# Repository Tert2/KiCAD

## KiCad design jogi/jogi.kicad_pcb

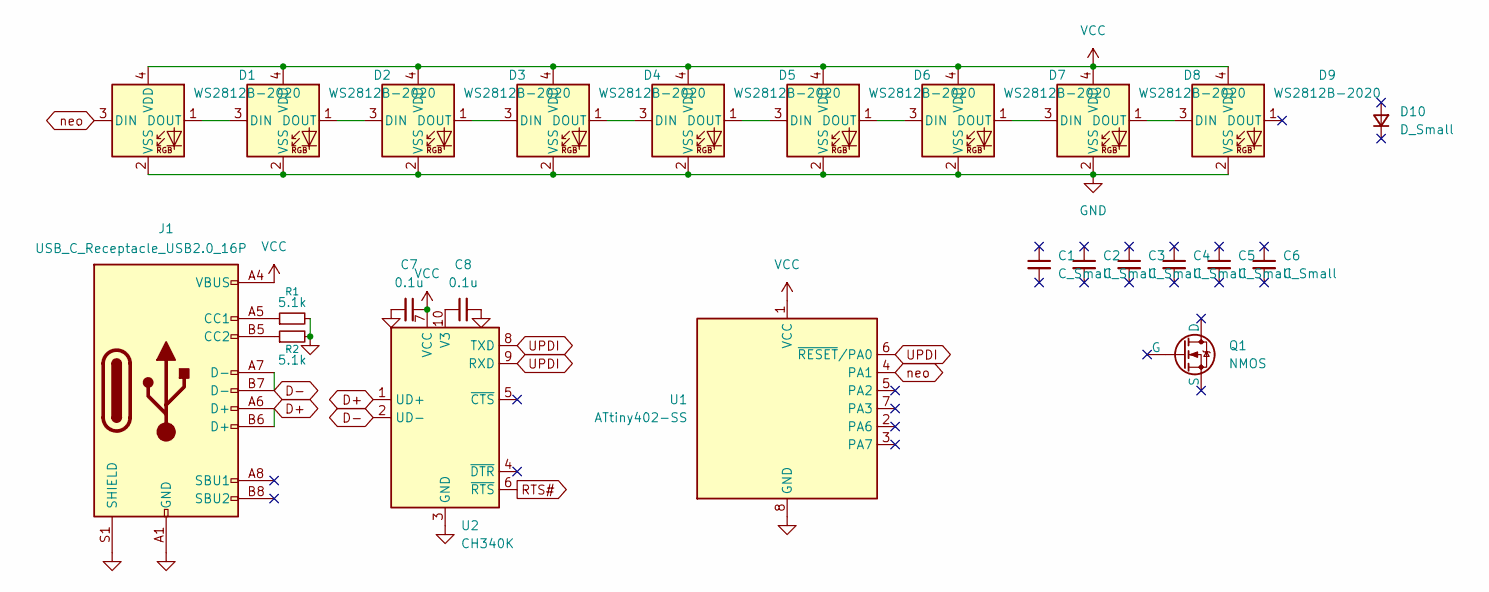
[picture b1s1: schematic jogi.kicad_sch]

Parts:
C1: C_Small; C_1210_3225Metric
C2: C_Small; C_1206_3216Metric
C3: C_Small; C_0805_2012Metric
C4: C_Small; C_0603_1608Metric
C5: C_Small; C_0402_1005Metric
C6: C_Small; C_01005_0402Metric
C7, C8: 0.1u; C_0603_1608Metric_Pad1.08x0.95mm_HandSolder
D1, D2, D3, D4, D5, D6, D7, D8, D9: WS2812B-2020; LED_WS2812B-2020_PLCC4_2.0x2.0mm
D10: D_Small; Nexperia_CFP3_SOD-123W
J1: USB_C_Receptacle_USB2.0_16P; USB_C_Receptacle_GCT_USB4105-xx-A_16P_TopMnt_Horizontal
Q1: NMOS; TSOT-23
R1, R2: 5.1k; R_0603_1608Metric_Pad0.98x0.95mm_HandSolder
U1: ATtiny402-SS; SOIC-8_3.9x4.9mm_P1.27mm
U2: CH340K; SSOP-10-1EP_3.9x4.9mm_P1mm_EP2.1x3.3mm

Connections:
D+: J1.A6 (D+), J1.B6 (D+), U2.1 (UD+)
D-: J1.A7 (D-), J1.B7 (D-), U2.2 (UD-)
GND: C7.2, C8.2, D1.2 (VSS), D2.2 (VSS), D3.2 (VSS), D4.2 (VSS), D5.2 (VSS), D6.2 (VSS), D7.2 (VSS), D8.2 (VSS), D9.2 (VSS), J1.A1 (GND), J1.A12 (GND), J1.B1 (GND), J1.B12 (GND), J1.S1 (SHIELD), R1.2, R2.2, U1.8 (GND), U2.3 (GND), U2.11 (GND)
unnamed: D1.1 (DOUT), D2.3 (DIN)
unnamed: D2.1 (DOUT), D3.3 (DIN)
unnamed: D3.1 (DOUT), D4.3 (DIN)
unnamed: D4.1 (DOUT), D5.3 (DIN)
unnamed: D5.1 (DOUT), D6.3 (DIN)
unnamed: D6.1 (DOUT), D7.3 (DIN)
unnamed: D7.1 (DOUT), D8.3 (DIN)
unnamed: D8.1 (DOUT), D9.3 (DIN)
unnamed: J1.A5 (CC1), R1.1
unnamed: J1.B5 (CC2), R2.1
unnamed: C8.1, U2.10 (V3)
RTS#: U2.6 (~RTS)
UPDI: U1.6 (~RESET/PA0), U2.8 (TXD), U2.9 (RXD)
VCC: C7.1, D1.4 (VDD), D2.4 (VDD), D3.4 (VDD), D4.4 (VDD), D5.4 (VDD), D6.4 (VDD), D7.4 (VDD), D8.4 (VDD), D9.4 (VDD), J1.A4 (VBUS), J1.A9 (VBUS), J1.B4 (VBUS), J1.B9 (VBUS), U1.1 (VCC), U2.7 (VCC)
neo: D1.3 (DIN), U1.4 (PA1)

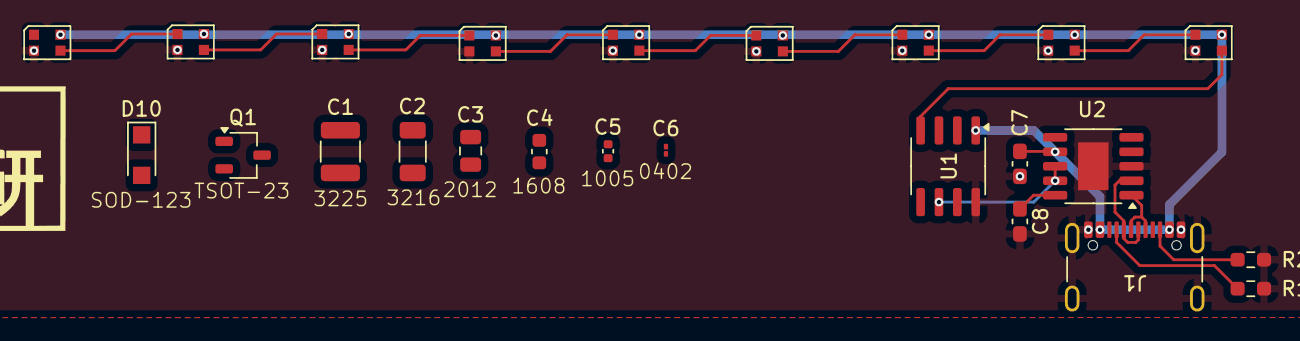
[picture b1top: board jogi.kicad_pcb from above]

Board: 2 copper layers, 24 parts (0 on the bottom side), 17 nets.

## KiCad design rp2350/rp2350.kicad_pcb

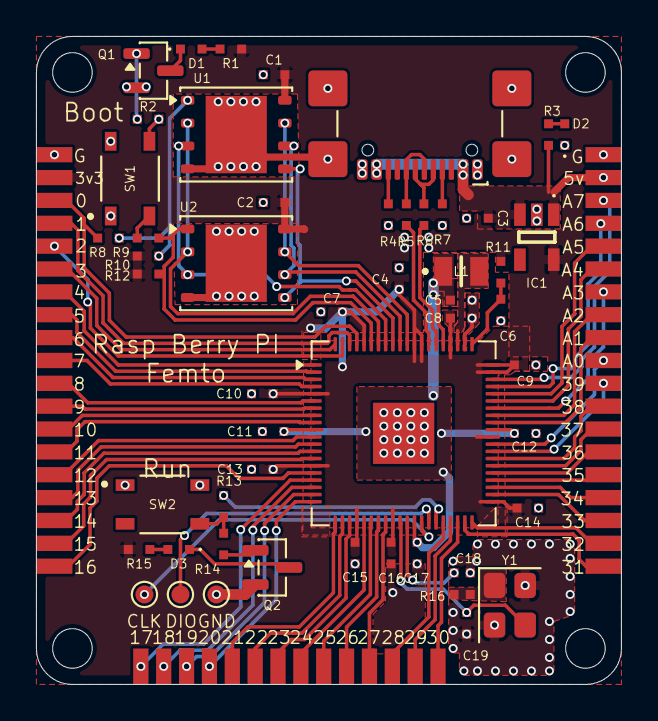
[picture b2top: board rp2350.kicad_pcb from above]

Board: 2 copper layers, 32.5 x 36.0 mm, 59 parts (0 on the bottom side), 83 nets.

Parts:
C1, C2, C4, C7, C10, C11, C12, C13, C14, C15, C16, C17: 0.1u; 1005
C3, C9: 1u; 1005
C5, C6, C8: 4.7u; 1005
C18, C19: 15p; 1005
D1, D2, D3: LED_Small; D1005
IC1: RT9080N-08GJ5; SOT94P280X100-5N
J1: USB_C_Receptacle_USB2.0_16P; USB_C_Receptacle_GCT_USB4110
J2, J3: Conn_01x19_Pin; 01x19
J4, J5, J6: Conn_01x01_Pin; TestPoint_Pad_D1.0mm
J7: Conn_01x14_Pin; 01x14
L1: AOTA-B201610S3R3-101-T; AOTAB201610S3R3101T
Q1, Q2: BSS138; SOT-23
R1, R3, R9, R13, R15, R16: 1k; R1005
R2, R14: 100k; R1005
R4, R7: 4.7k; R1005
R5, R6: 27; R1005
R8, R10, R12: 10k; R1005
R11: 33; R1005
REF1, REF2, REF3, REF4: MountingHole_2.2mm_M2
SW1, SW2: SKRPABE010; SW_SKRPABE010
U1, U2: W25Q128JVP; WSON-8-1EP_6x5mm_P1.27mm_EP3.4x4.3mm
U3: RP2350B; QFN-80-1EP_10x10mm_P0.4mm_EP3.4x3.4mm
Y1: 12M; Crystal_SMD_3225-4Pin_3.2x2.5mm

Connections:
+1V1: C5.1, C11.2, C12.2, C17.2, L1.1, U3.10 (DVDD), U3.32 (DVDD), U3.51 (DVDD), U3.65 (VREG_FB)
+3V3: C1.1, C2.1, C4.2, C7.2, C8.1, C9.2, C10.2, C13.2, C14.2, C15.2, C16.2, IC1.5 (VOUT), J2.18, R1.2, R10.2, R11.2, R12.2, R15.2, U1.8 (VCC), U2.8 (VCC), U3.5 (IOVDD), U3.15 (IOVDD), U3.24 (IOVDD), U3.29 (IOVDD), U3.41 (IOVDD), U3.50 (IOVDD), U3.59 (ADC_AVDD), U3.60 (IOVDD), U3.64 (VREG_VIN), U3.68 (USB_OTP_VDD), U3.69 (QSPI_IOVDD), U3.76 (IOVDD)
/ADC0: J3.10, U3.49 (GPIO40/ADC0)
/ADC1: J3.9, U3.52 (GPIO41/ADC1)
/ADC2: J3.8, U3.53 (GPIO42/ADC2)
/ADC3: J3.7, U3.54 (GPIO43/ADC3)
/ADC4: J3.6, U3.55 (GPIO44/ADC4)
/ADC5: J3.5, U3.56 (GPIO45/ADC5)
/ADC6: J3.4, U3.57 (GPIO46/ADC6)
/ADC7: J3.3, U3.58 (GPIO47/ADC7)
/FLASH2_SS: R8.2, R10.1, U1.1 (~CS)
/FLASH_SS: R9.2, R12.1, U2.1 (~CS), U3.75 (~QSPI_SS)
/IO0: J2.17, R8.1, U3.77 (GPIO0)
/IO1: J2.16, U3.78 (GPIO1)
/IO2: J2.15, U3.79 (GPIO2)
/IO3: J2.14, U3.80 (GPIO3)
/IO4: J2.13, U3.1 (GPIO4)
/IO5: J2.12, U3.2 (GPIO5)
/IO6: J2.11, U3.3 (GPIO6)
/IO7: J2.10, U3.4 (GPIO7)
/IO8: J2.9, U3.6 (GPIO8)
/IO9: J2.8, U3.7 (GPIO9)
/IO10: J2.7, U3.8 (GPIO10)
/IO11: J2.6, U3.9 (GPIO11)
/IO12: J2.5, U3.11 (GPIO12)
/IO13: J2.4, U3.12 (GPIO13)
/IO14: J2.3, U3.13 (GPIO14)
/IO15: J2.2, U3.14 (GPIO15)
/IO16: J2.1, U3.16 (GPIO16)
/IO17: J7.14, U3.17 (GPIO17)
/IO18: J7.13, U3.18 (GPIO18)
/IO19: J7.12, U3.19 (GPIO19)
/IO20: J7.11, U3.20 (GPIO20)
/IO21: J7.10, U3.21 (GPIO21)
/IO22: J7.9, U3.22 (GPIO22)
/IO23: J7.8, U3.23 (GPIO23)
/IO24: J7.7, U3.25 (GPIO24)
/IO25: J7.6, U3.26 (GPIO25)
/IO26: J7.5, U3.27 (GPIO26)
/IO27: J7.4, U3.28 (GPIO27)
/IO28: J7.3, U3.36 (GPIO28)
/IO29: J7.2, U3.37 (GPIO29)
/IO30: J7.1, U3.38 (GPIO30)
/IO31: J3.19, U3.39 (GPIO31)
/IO32: J3.18, U3.40 (GPIO32)
/IO33: J3.17, U3.42 (GPIO33)
/IO34: J3.16, U3.43 (GPIO34)
/IO35: J3.15, U3.44 (GPIO35)
/IO36: J3.14, U3.45 (GPIO36)
/IO37: J3.13, U3.46 (GPIO37)
/IO38: J3.12, U3.47 (GPIO38)
/IO39: J3.11, U3.48 (GPIO39)
/QSPI_SCLK: U1.6 (CLK), U2.6 (CLK), U3.71 (QSPI_SCLK)
/QSPI_SD0: U1.5 (DI/IO_{0}), U2.5 (DI/IO_{0}), U3.72 (QSPI_SD0)
/QSPI_SD1: U1.2 (DO/IO_{1}), U2.2 (DO/IO_{1}), U3.74 (QSPI_SD1)
/QSPI_SD2: U1.3 (~WP/IO_{2}), U2.3 (~WP/IO_{2}), U3.73 (QSPI_SD2)
/QSPI_SD3: U1.7 (~HOLD/~RESET/IO_{3}), U2.7 (~HOLD/~RESET/IO_{3}), U3.70 (QSPI_SD3)
/RUN: R13.2, U3.35 (RUN)
/SWCLK: J4.1, U3.33 (SWCLK)
/SWDIO: J5.1, U3.34 (SWDIO)
/XIN: C19.2, U3.30 (XIN), Y1.3
/XOUT: R16.2, U3.31 (XOUT)
/xout: C18.2, R16.1, Y1.1
D+: R5.2, U3.67 (USB_DP)
D-: R6.2, U3.66 (USB_DM)
GND: C1.2, C2.2, C3.1, C4.1, C5.2, C6.2, C7.1, C8.2, C9.1, C10.1, C11.1, C12.1, C13.1, C14.1, C15.1, C16.1, C17.1, C18.1, C19.1, D2.1 (K), IC1.2 (GND), J1.A1 (GND), J1.A12 (GND), J1.B1 (GND), J1.B12 (GND), J1.S1 (SHIELD), J2.19, J3.1, J6.1, Q1.2 (S), Q2.2 (S), R4.2, R7.2, SW1.1, SW1.2, SW2.1, SW2.2, U1.4 (GND), U1.9 (EP), U2.4 (GND), U2.9 (EP), U3.62 (VREG_PGND), U3.81 (GND), Y1.2 (G), Y1.4 (G)
unnamed: D3.2 (A), R15.1
unnamed: D3.1 (K), Q2.3 (D)
unnamed: D1.2 (A), R1.1
unnamed: D1.1 (K), Q1.3 (D)
unnamed: D2.2 (A), R3.1
unnamed: J1.A5 (CC1), R7.1
unnamed: J1.B5 (CC2), R4.1
unnamed: J1.A6 (D+), J1.B6 (D+), R5.1
unnamed: J1.A7 (D-), J1.B7 (D-), R6.1
unnamed: Q2.1 (G), R14.1
unnamed: Q1.1 (G), R2.2
unnamed: R13.1, R14.2, SW2.4 (A)
unnamed: R2.1, SW1.4 (A)
unnamed: R9.1, SW1.3 (K)
unnamed: C6.1, R11.1, U3.61 (VREG_AVDD)
unnamed: L1.2, U3.63 (VREG_LX)
VBUS: C3.2, IC1.1 (VIN), IC1.3 (EN), J1.A4 (VBUS), J1.A9 (VBUS), J1.B4 (VBUS), J1.B9 (VBUS), J3.2, R3.2

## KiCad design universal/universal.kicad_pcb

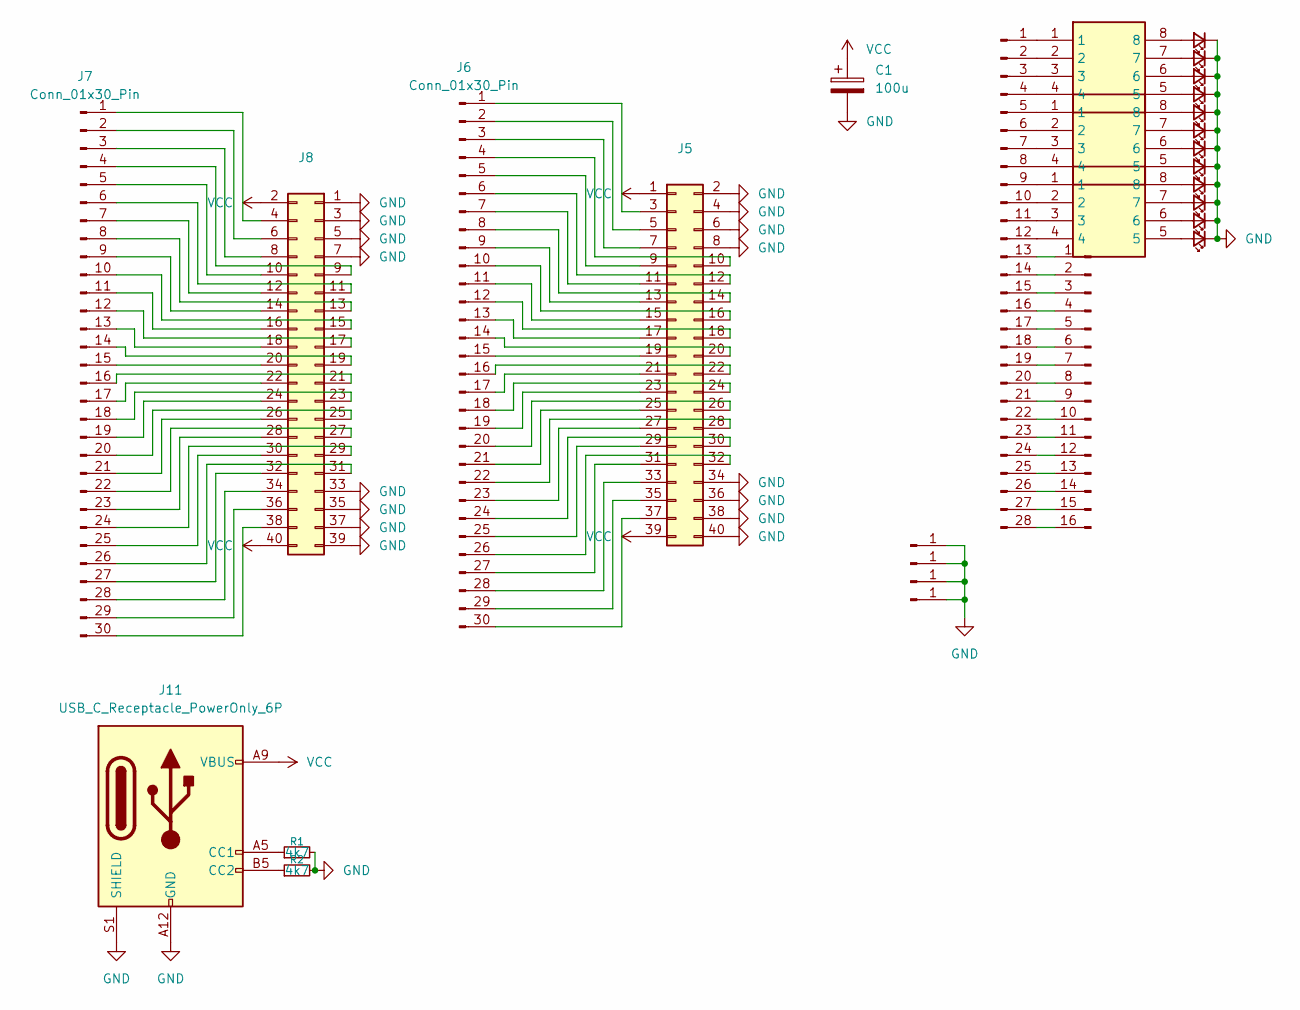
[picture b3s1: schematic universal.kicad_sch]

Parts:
C1: 100u; CP_Radial_D6.3mm_P2.50mm
D1, D2, D3, D4, D5, D6, D7, D8, D9, D10, D11, D12: LED_Small; LED_0603_1608Metric
J1, J2, J3, J4: Conn_01x01_Pin; MountingHole_3.2mm_M3_DIN965_Pad_TopBottom
J5, J8: Conn_02x20_Odd_Even; PinHeader_2x20_P2.54mm_Vertical
J6, J7: Conn_01x30_Pin; SMD_uni
J9: Conn_01x28_Pin; SMD_28_uni
J10: Conn_01x16_Pin; PinHeader_1x16_P2.54mm_Vertical
J11: USB_C_Receptacle_PowerOnly_6P; USB_C_Receptacle_GCT_USB4125-xx-x-0190_6P_TopMnt_Horizontal
R1, R2: 4k7; R_0603_1608Metric
RN1, RN2, RN3: BCN164AB220J7; Manufacturer_Part_Number BCN164AB220J7; Mouser Part Number 858-BCN164AB220J7

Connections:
GND: C1.2, D1.1 (K), D2.1 (K), D3.1 (K), D4.1 (K), D5.1 (K), D6.1 (K), D7.1 (K), D8.1 (K), D9.1 (K), D10.1 (K), D11.1 (K), D12.1 (K), J1.1, J2.1, J3.1, J4.1, J5.2, J5.4, J5.6, J5.8, J5.34, J5.36, J5.38, J5.40, J8.1, J8.3, J8.5, J8.7, J8.33, J8.35, J8.37, J8.39, J11.A12 (GND), J11.B12 (GND), J11.S1 (SHIELD), R1.2, R2.2
unnamed: D1.2 (A), RN1.8
unnamed: D2.2 (A), RN1.7
unnamed: D3.2 (A), RN1.6
unnamed: D4.2 (A), RN1.5
unnamed: D5.2 (A), RN2.8
unnamed: D6.2 (A), RN2.7
unnamed: D7.2 (A), RN2.6
unnamed: D8.2 (A), RN2.5
unnamed: D9.2 (A), RN3.8
unnamed: D10.2 (A), RN3.7
unnamed: D11.2 (A), RN3.6
unnamed: D12.2 (A), RN3.5
unnamed: J5.3, J6.1
unnamed: J5.5, J6.2
unnamed: J5.7, J6.3
unnamed: J5.9, J6.5
unnamed: J5.10, J6.4
unnamed: J5.11, J6.7
unnamed: J5.12, J6.6
unnamed: J5.13, J6.9
unnamed: J5.14, J6.8
unnamed: J5.15, J6.11
unnamed: J5.16, J6.10
unnamed: J5.17, J6.13
unnamed: J5.18, J6.12
unnamed: J5.19, J6.15
unnamed: J5.20, J6.14
unnamed: J5.21, J6.17
unnamed: J5.22, J6.16
unnamed: J5.23, J6.19
unnamed: J5.24, J6.18
unnamed: J5.25, J6.21
unnamed: J5.26, J6.20
unnamed: J5.27, J6.23
unnamed: J5.28, J6.22
unnamed: J5.29, J6.25
unnamed: J5.30, J6.24
unnamed: J5.31, J6.27
unnamed: J5.32, J6.26
unnamed: J5.33, J6.28
unnamed: J5.35, J6.29
unnamed: J5.37, J6.30
unnamed: J7.1, J8.4
unnamed: J7.2, J8.6
unnamed: J7.3, J8.8
unnamed: J7.4, J8.9
unnamed: J7.5, J8.10
unnamed: J7.6, J8.11
unnamed: J7.7, J8.12
unnamed: J7.8, J8.13
unnamed: J7.9, J8.14
unnamed: J7.10, J8.15
unnamed: J7.11, J8.16
unnamed: J7.12, J8.17
unnamed: J7.13, J8.18
unnamed: J7.14, J8.19
unnamed: J7.15, J8.20
unnamed: J7.16, J8.21
unnamed: J7.17, J8.22
unnamed: J7.18, J8.23
unnamed: J7.19, J8.24
unnamed: J7.20, J8.25
unnamed: J7.21, J8.26
unnamed: J7.22, J8.27
unnamed: J7.23, J8.28
unnamed: J7.24, J8.29
unnamed: J7.25, J8.30
unnamed: J7.26, J8.31
unnamed: J7.27, J8.32
unnamed: J7.28, J8.34
unnamed: J7.29, J8.36
unnamed: J7.30, J8.38
unnamed: J9.1, RN1.1
unnamed: J9.2, RN1.2
unnamed: J9.3, RN1.3
unnamed: J9.4, RN1.4
unnamed: J9.5, RN2.1
unnamed: J9.6, RN2.2
unnamed: J9.7, RN2.3
unnamed: J9.8, RN2.4
unnamed: J9.9, RN3.1
unnamed: J9.10, RN3.2
unnamed: J9.11, RN3.3
unnamed: J9.12, RN3.4
unnamed: J9.13, J10.1
unnamed: J9.14, J10.2
unnamed: J9.15, J10.3
unnamed: J9.16, J10.4
unnamed: J9.17, J10.5
unnamed: J9.18, J10.6
unnamed: J9.19, J10.7
unnamed: J9.20, J10.8
unnamed: J9.21, J10.9
unnamed: J9.22, J10.10
unnamed: J9.23, J10.11
unnamed: J9.24, J10.12
unnamed: J9.25, J10.13
unnamed: J9.26, J10.14
unnamed: J9.27, J10.15
unnamed: J9.28, J10.16
unnamed: J11.A5 (CC1), R1.1
unnamed: J11.B5 (CC2), R2.1
VCC: C1.1, J5.1, J5.39, J8.2, J8.40, J11.A9 (VBUS), J11.B9 (VBUS)

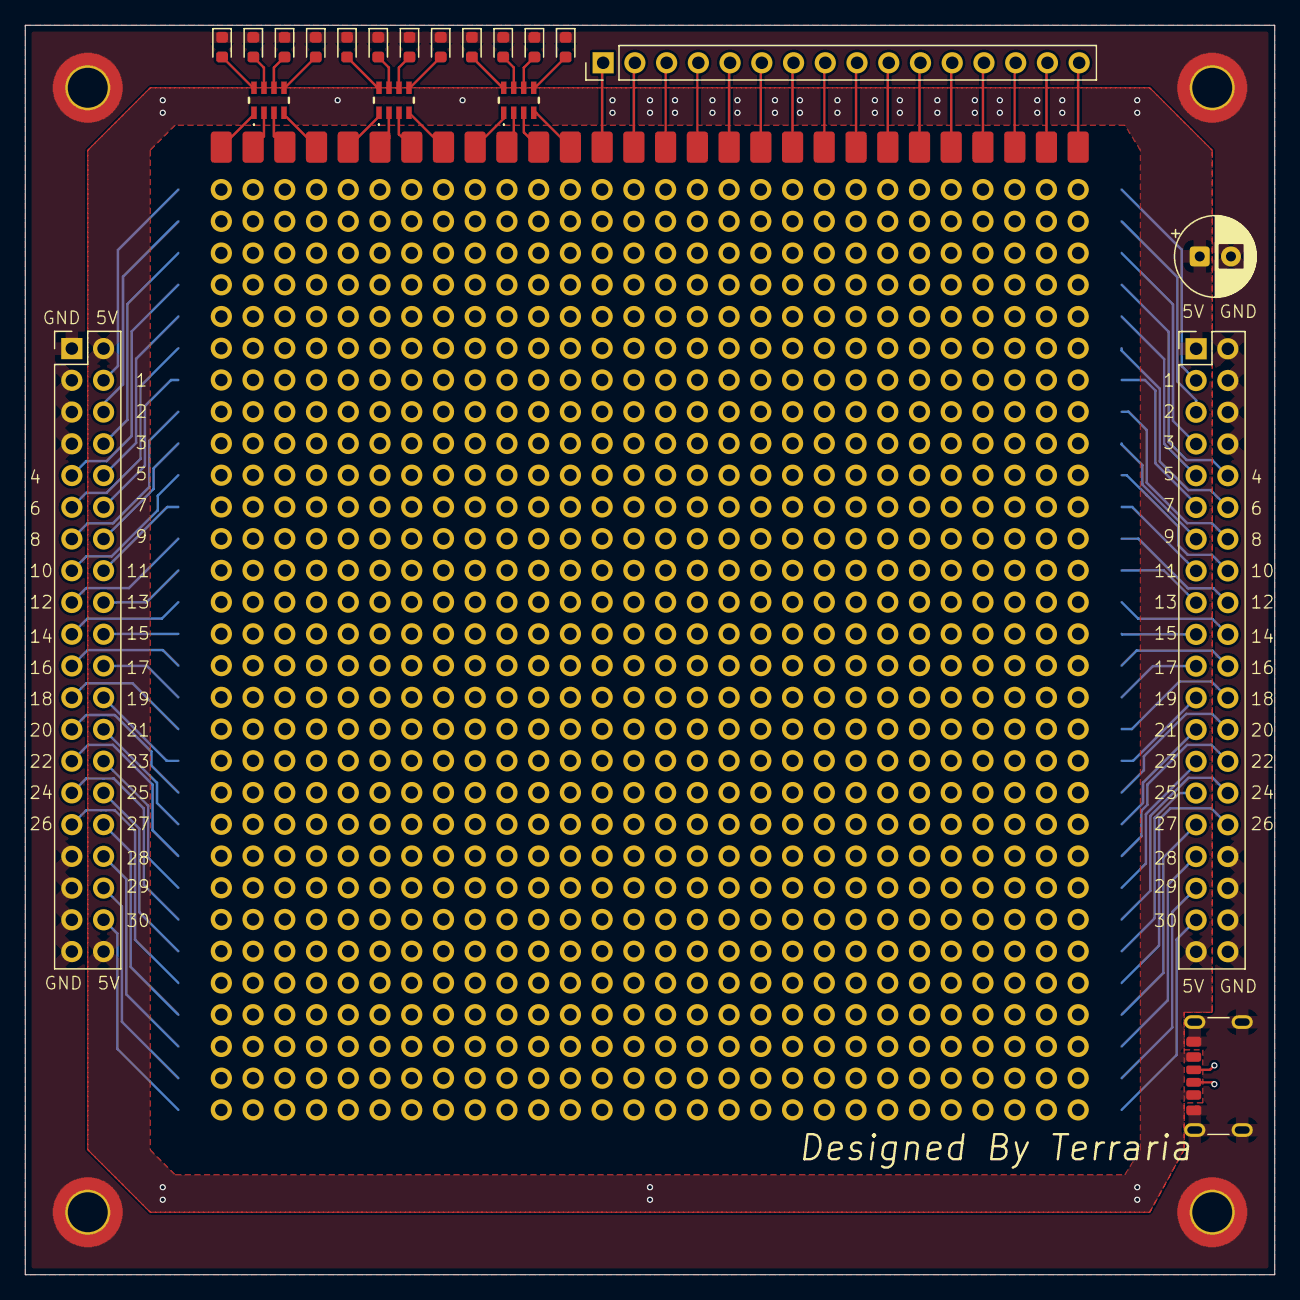
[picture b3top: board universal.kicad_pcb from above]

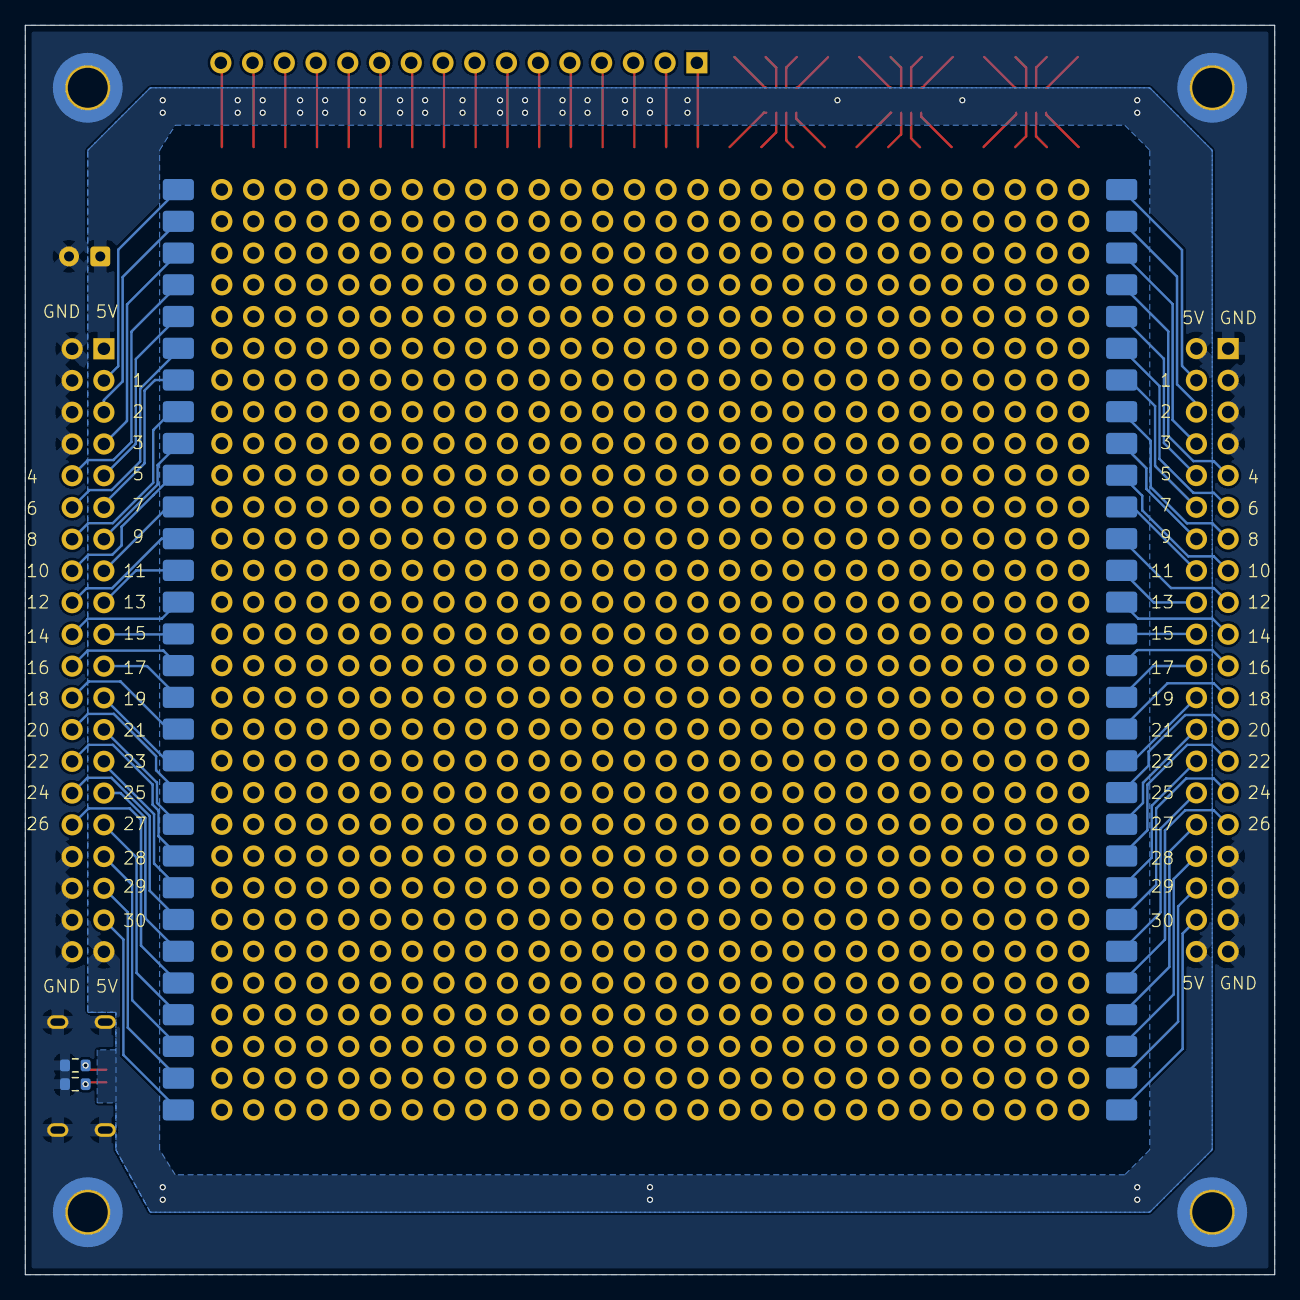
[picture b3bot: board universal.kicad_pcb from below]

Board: 2 copper layers, 100.0 x 100.0 mm, 29 parts (4 on the bottom side), 104 nets.

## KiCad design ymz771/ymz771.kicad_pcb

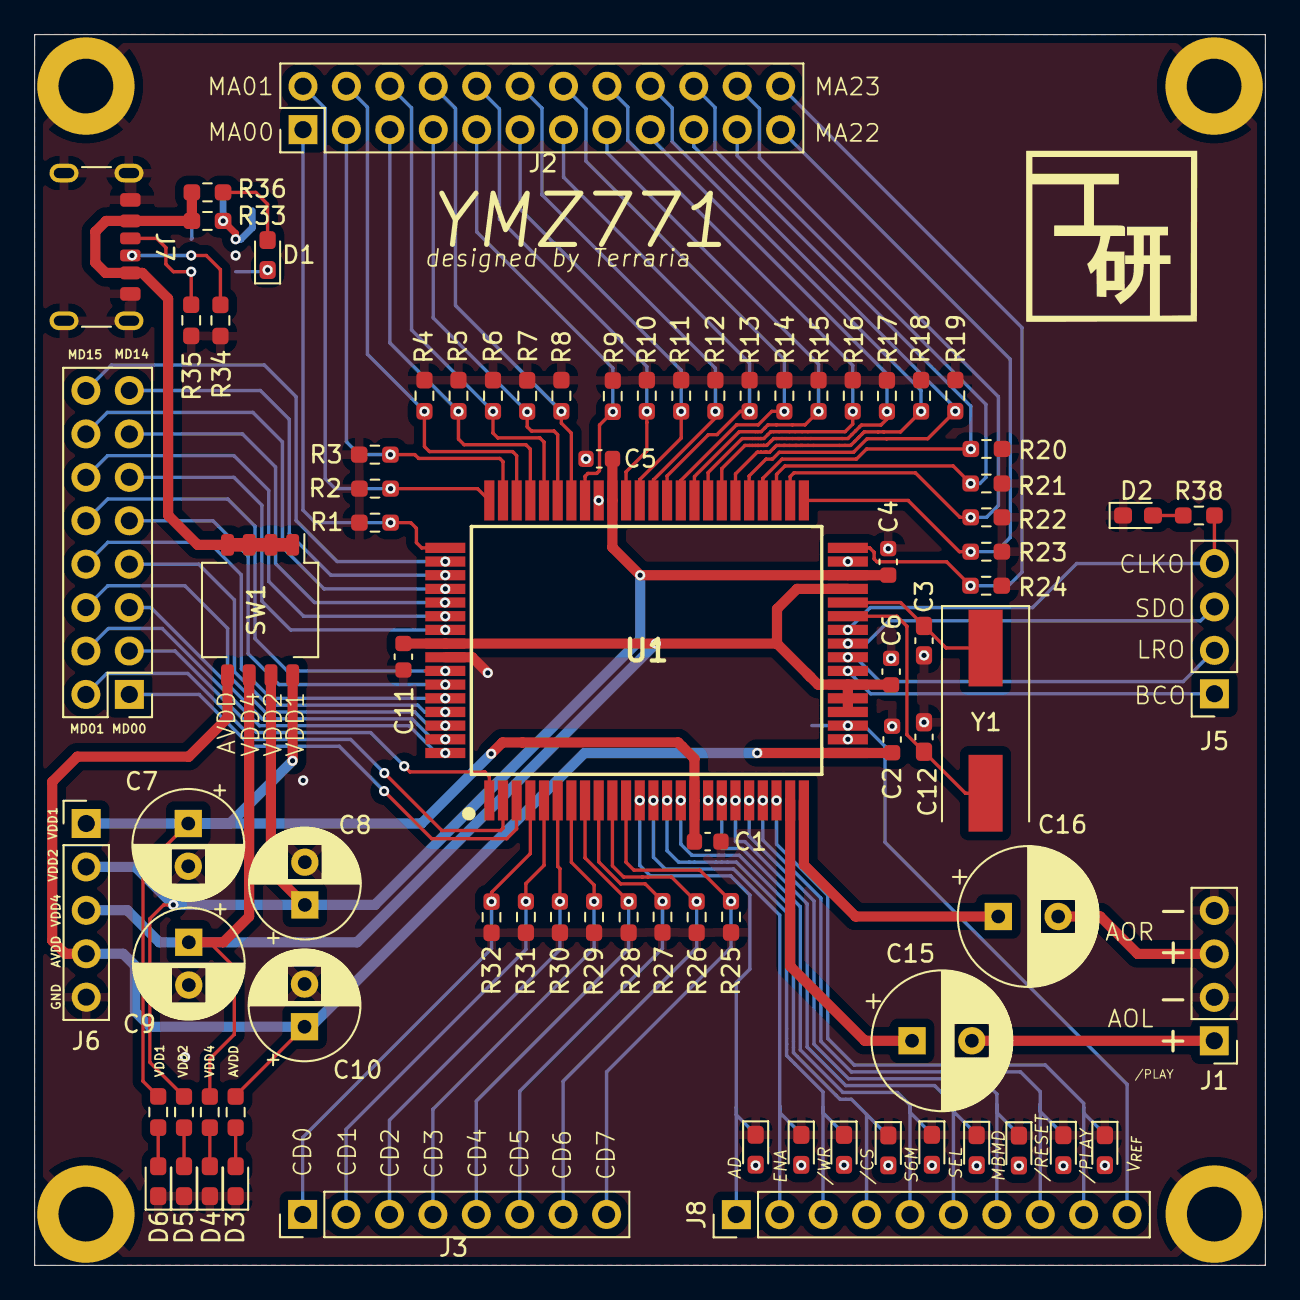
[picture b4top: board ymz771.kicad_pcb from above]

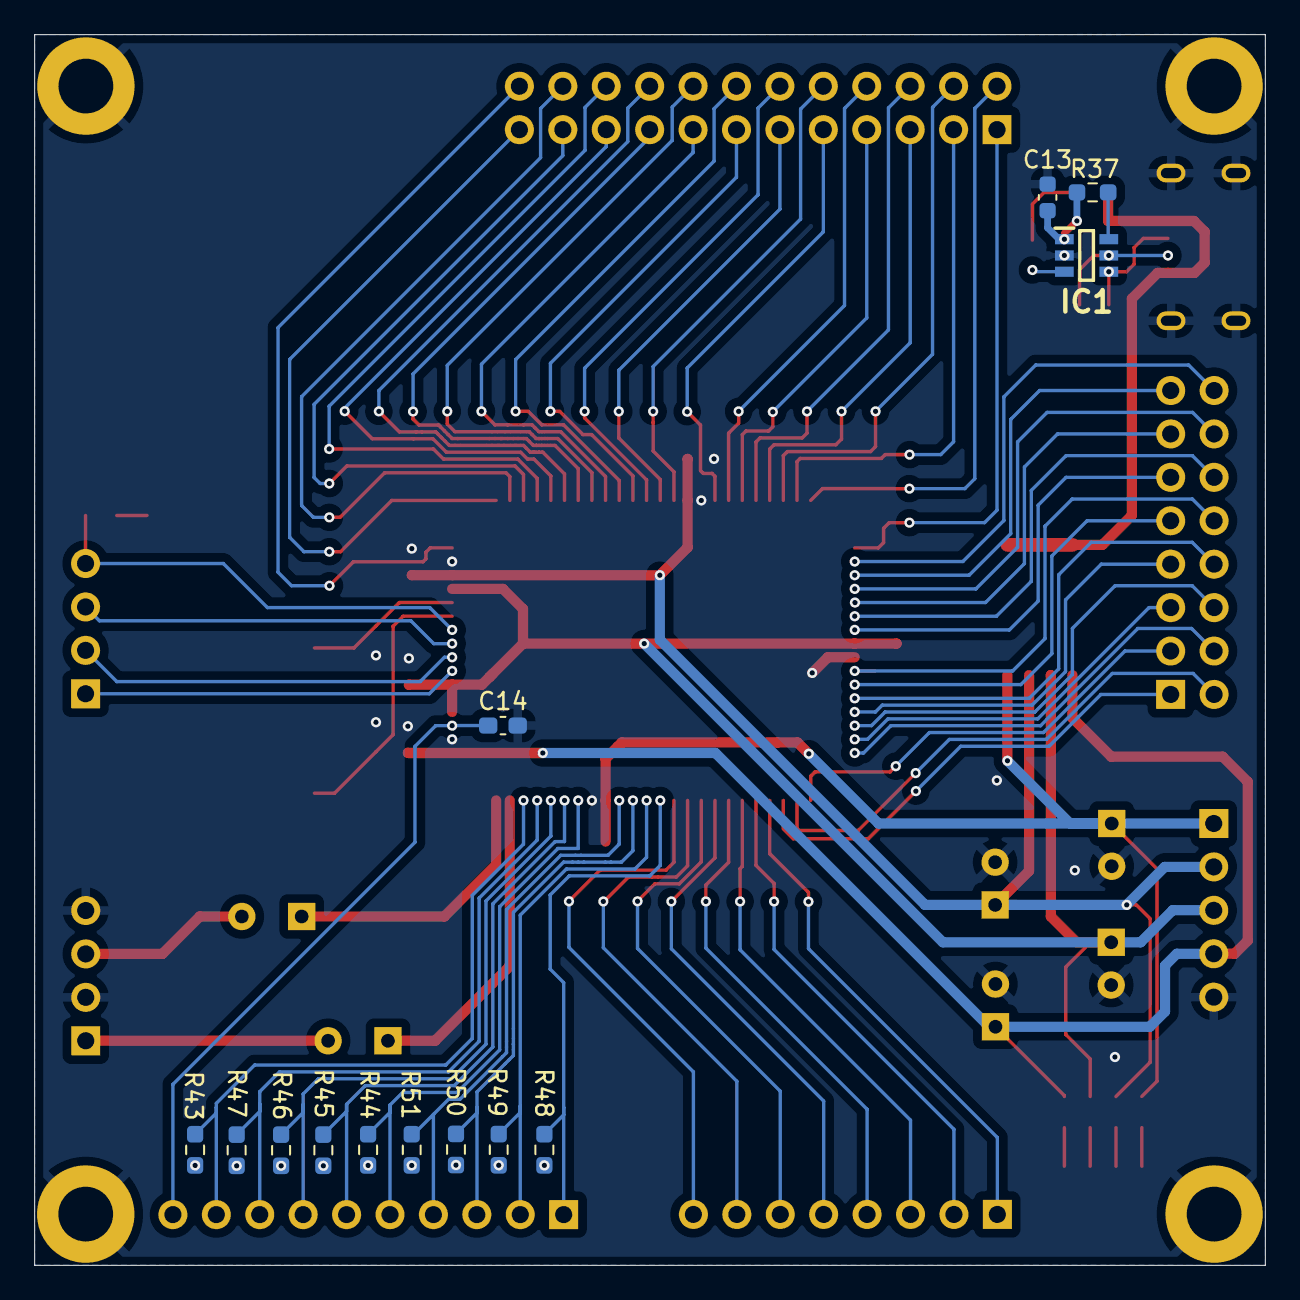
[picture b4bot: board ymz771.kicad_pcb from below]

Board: 2 copper layers, 72.0 x 72.0 mm, 94 parts (13 on the bottom side), 94 nets.

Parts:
C1, C2, C4, C5, C6, C11, C13: C_Small; C_0603_1608Metric
C3, C12, C14: 20n; C_0603_1608Metric_Pad1.08x0.95mm_HandSolder
C7, C8, C9, C10: C_Polarized_Small; CP_Radial_D6.3mm_P2.50mm
C15, C16: C_Polarized_Small; CP_Radial_D8.0mm_P3.50mm
D1, D2, D3, D4, D5, D6, D7, D8, D9, D10, D11, D12, D13, D14, D15: LED_Small; LED_0603_1608Metric_Pad1.05x0.95mm_HandSolder
IC1: CH221K; SOT95P280X120-6N
J1: Conn_01x04_Pin; PinHeader_1x04_P2.54mm_Vertical
J2: Conn_02x12_Counter_Clockwise; PinHeader_2x12_P2.54mm_Vertical
J3: Conn_01x08_Pin; PinHeader_1x08_P2.54mm_Vertical
J4: Conn_02x08_Counter_Clockwise; PinHeader_2x08_P2.54mm_Vertical
J5: Conn_01x04_Pin; PinSocket_1x04_P2.54mm_Vertical
J6: Conn_01x05_Pin; PinHeader_1x05_P2.54mm_Vertical
J7: USB_C_Receptacle_PowerOnly_6P; USB_C_Receptacle_GCT_USB4125-xx-x_6P_TopMnt_Horizontal
J8: Conn_01x10_Pin; PinHeader_1x10_P2.54mm_Vertical
R1, R2, R3, R4, R5, R6, R7, R8, R9, R10, R11, R12, R13, R14, R15, R16, R17, R18, R19, R20, R21, R22, R23, R24, R25, R26, R27, R28, R29, R30, R31, R32, R37: 10k; R_0603_1608Metric_Pad0.98x0.95mm_HandSolder
R33: 1k; R_0603_1608Metric_Pad0.98x0.95mm_HandSolder
R34, R35: 5.1k; R_0603_1608Metric_Pad0.98x0.95mm_HandSolder
R36, R38, R39, R40, R41, R42, R43, R44, R45, R46, R47, R48, R49, R50, R51: 100k; R_0603_1608Metric_Pad0.98x0.95mm_HandSolder
SW1: SW_DIP_x04; SW_DIP_SPSTx04_Slide_KingTek_DSHP04TS_W7.62mm_P1.27mm
U1: YMZ771-F
Y1: Crystal; Crystal_SMD_HC49-SD

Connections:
+5V: J7.A9 (VBUS), J7.B9 (VBUS), R33.1, R36.2, SW1.1, SW1.2, SW1.3, SW1.4
/AD: J8.1, R48.2, U1.12 (AD)
/AOL: C15.1, U1.23 (AOL)
/AOR: C16.1, U1.24 (AOR)
/BCO: J5.1, U1.31 (BCO)
/CLKO: J5.4, R38.2, U1.34 (CLKO)
/ENA: J8.2, R49.2, U1.13 (ENA)
/LRO: J5.2, U1.32 (LRO)
/MA00: J2.1, R1.1, U1.65 (MA00)
/MA01: J2.2, R2.1, U1.64 (MA01)
/MA02: J2.3, R3.1, U1.63 (MA02)
/MA03: J2.4, R4.1, U1.62 (MA03)
/MA04: J2.5, R5.1, U1.61 (MA04)
/MA05: J2.6, R6.1, U1.60 (MA05)
/MA06: J2.7, R7.1, U1.59 (MA06)
/MA07: J2.8, R8.1, U1.58 (MA07)
/MA08: J2.9, R9.1, U1.57 (MA08)
/MA09: J2.10, R10.1, U1.54 (MA09)
/MA10: J2.11, R11.1, U1.53 (MA10)
/MA11: J2.12, R12.1, U1.52 (MA11)
/MA12: J2.13, R13.1, U1.51 (MA12)
/MA13: J2.14, R14.1, U1.50 (MA13)
/MA14: J2.15, R15.1, U1.49 (MA14)
/MA15: J2.16, R16.1, U1.48 (MA15)
/MA16: J2.17, R17.1, U1.47 (MA16)
/MA17: J2.18, R18.1, U1.46 (MA17)
/MA18: J2.19, R19.1, U1.45 (MA18)
/MA19: J2.20, R20.1, U1.44 (MA19)
/MA20: J2.21, R21.1, U1.43 (MA20)
/MA21: J2.22, R22.1, U1.42 (MA21)
/MA22: J2.23, R23.1, U1.41 (MA22)
/MA23: J2.24, R24.1, U1.40 (MA23)
/MBMD: J8.7, R46.2, U1.20 (MBMD)
/MD00: J4.1, U1.3 (MD00)
/MD01: J4.2, U1.2 (MD01)
/MD02: J4.3, U1.1 (MD02)
/MD03: J4.4, U1.80 (MD03)
/MD04: J4.5, U1.79 (MD04)
/MD05: J4.6, U1.78 (MD05)
/MD06: J4.7, U1.77 (MD06)
/MD07: J4.8, U1.76 (MD07)
/MD08: J4.9, U1.75 (MD08)
/MD09: J4.10, U1.74 (MD09)
/MD10: J4.11, U1.71 (MD10)
/MD11: J4.12, U1.70 (MD11)
/MD12: J4.13, U1.69 (MD12)
/MD13: J4.14, U1.68 (MD13)
/MD14: J4.15, U1.67 (MD14)
/MD15: J4.16, U1.66 (MD15)
/S6M: J8.5, R44.2, U1.18 (S6M)
/SDO: J5.3, U1.33 (SDO)
/SEL: J8.6, R45.2, U1.19 (SEL)
/Vref: C14.1, J8.10, U1.27 (V_{REF})
//CS: J8.4, R51.2, U1.15 (/CS)
//PLAY: J8.9, R43.2, U1.22 (/PLAY)
//RESET: J8.8, R47.2, U1.21 (/RESET)
//WR: J8.3, R50.2, U1.14 (/WR)
AVDD: C2.1, C10.1, J6.4, R39.2, SW1.5, U1.25 (AV_{DD})
GND: C1.2, C2.2, C3.2, C4.2, C5.2, C6.2, C7.2, C8.2, C9.2, C10.2, C11.2, C12.2, C13.2, C14.2, D2.1 (K), D3.1 (K), D4.1 (K), D5.1 (K), D6.1 (K), D7.1 (K), D8.1 (K), D9.1 (K), D10.1 (K), D11.1 (K), D12.1 (K), D13.1 (K), D14.1 (K), D15.1 (K), IC1.2 (GND), J1.2, J1.4, J6.5, J7.A12 (GND), J7.B12 (GND), J7.S1 (SHIELD), R1.2, R2.2, R3.2, R4.2, R5.2, R6.2, R7.2, R8.2, R9.2, R10.2, R11.2, R12.2, R13.2, R14.2, R15.2, R16.2, R17.2, R18.2, R19.2, R20.2, R21.2, R22.2, R23.2, R24.2, R25.2, R26.2, R27.2, R28.2, R29.2, R30.2, R31.2, R32.2, R34.1, R35.1, U1.17 (V_{SS}1), U1.26 (AV_{SS}), U1.39 (V_{SS}2), U1.56 (V_{SS}3), U1.73 (V_{SS}4)
unnamed: D1.2 (A), R36.1
unnamed: D1.1 (K), IC1.3 (PG)
unnamed: D2.2 (A), R38.1
unnamed: D3.2 (A), R39.1
unnamed: D4.2 (A), R40.1
unnamed: D5.2 (A), R41.1
unnamed: D6.2 (A), R42.1
unnamed: D7.2 (A), R43.1
unnamed: D8.2 (A), R44.1
unnamed: D9.2 (A), R45.1
unnamed: D10.2 (A), R46.1
unnamed: D11.2 (A), R47.1
unnamed: D12.2 (A), R48.1
unnamed: D13.2 (A), R49.1
unnamed: D14.2 (A), R50.1
unnamed: D15.2 (A), R51.1
unnamed: IC1.4 (CC1), J7.A5 (CC1), R35.2
unnamed: IC1.5 (CC2), J7.B5 (CC2), R34.2
unnamed: IC1.6 (CFG), R37.1
unnamed: C13.1, IC1.1 (VDD), R33.2, R37.2
unnamed: C15.2, J1.1
unnamed: C16.2, J1.3
unnamed: J3.1, R32.1, U1.4 (CD0)
unnamed: J3.2, R31.1, U1.5 (CD1)
unnamed: J3.3, R30.1, U1.6 (CD2)
unnamed: J3.4, R29.1, U1.7 (CD3)
unnamed: J3.5, R28.1, U1.8 (CD4)
unnamed: J3.6, R27.1, U1.9 (CD5)
unnamed: J3.7, R26.1, U1.10 (CD6)
unnamed: J3.8, R25.1, U1.11 (CD7)
unnamed: C3.1, U1.36 (XI), Y1.1
unnamed: C12.1, U1.35 (XO), Y1.2
VDD1: C1.1, C7.1, J6.1, R42.2, SW1.8, U1.16 (V_{DD}1)
VDD2: C4.1, C5.1, C8.1, J6.2, R41.2, SW1.7, U1.38 (V_{DD}2), U1.55 (V_{DD}3)
VDD4: C6.1, C9.1, C11.1, J6.3, R40.2, SW1.6, U1.28 (/TEST0), U1.29 (/TEST1), U1.30 (V_{DD}5), U1.37 (/TEST2), U1.72 (V_{DD}4)
